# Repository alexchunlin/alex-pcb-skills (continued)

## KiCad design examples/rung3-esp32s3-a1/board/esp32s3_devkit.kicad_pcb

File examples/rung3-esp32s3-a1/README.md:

# ESP32-S3 Devkit, rev A

An open-hardware ESP32-S3 board with no module: the chip, crystal, RF match, chip antenna and power all sit on a 60 x 26 mm four-layer board. Flash it over USB-C with nothing else attached. Two 0.1 inch rows, 0.9 inch apart, fit a breadboard.

| | |
|---|---|
| Chip | ESP32-S3FH4R2, dual LX7, 2.4 GHz Wi-Fi, Bluetooth LE |
| Memory | 4 MB flash, 2 MB PSRAM, in package |
| Power | USB-C or 5 V on J2.1, 3.3 V LDO, 800 mA rated |
| Antenna | Johanson 2450AT18D0100 ceramic, on the short edge |
| I2C | Qwiic on J4, SDA GPIO17, SCL GPIO18, 10 k pull-ups, cut JP2 to remove |
| Buttons | RST, BOOT |
| LEDs | Power (red, cut JP1), user on GPIO9 (yellow) |
| Free GPIO on headers | 35, plus 3V3, 5V, EN, 2 GND |

The ESP32-S3 has no fixed I2C address. Any device you add on Qwiic sets its own.

## Pinout
Pin 1 is at the USB end. Details and strapping notes are in `PINMAP.md`.

| Pin | J1 | J2 |
|---|---|---|
| 1 | 3V3 | 5V |
| 2 | GPIO18 SCL | GND |
| 3 | GPIO17 SDA | GPIO21 |
| 4 | GPIO16 | GPIO47 |
| 5 | GPIO15 | GPIO48 |
| 6 | GPIO14 | GPIO33 |
| 7 | GPIO13 | GPIO34 |
| 8 | GPIO12 | GPIO35 |
| 9 | GPIO11 | GPIO36 |
| 10 | GPIO10 | GPIO37 |
| 11 | GPIO8 | GPIO38 |
| 12 | GPIO7 | GPIO39 |
| 13 | GPIO6 | GPIO40 |
| 14 | GPIO5 | GPIO41 |
| 15 | GPIO4 | GPIO42 |
| 16 | GPIO3 strap | GPIO43 U0TXD |
| 17 | GPIO2 | GPIO44 U0RXD |
| 18 | GPIO1 | GPIO45 strap |
| 19 | GPIO0 BOOT strap | GPIO46 strap |
| 20 | EN | GND |

## First flash
Hold BOOT, tap RST, release BOOT, then `esptool.py --chip esp32s3 write_flash ...` over USB. `BRINGUP.md` has the full sequence and the RF tuning steps. The RF match is unproven until someone tunes one on a VNA.

Keep hands and metal away from the antenna end. Do not pull GPIO45 high at reset: the flash runs at 3.3 V and needs VDD_SPI there.

## Files
`esp32s3_devkit.zen` and `blocks/` are the source. `tools/regen.sh` rebuilds the KiCad project and `fab/`. `DESIGN_LOG.md` has every calculation.

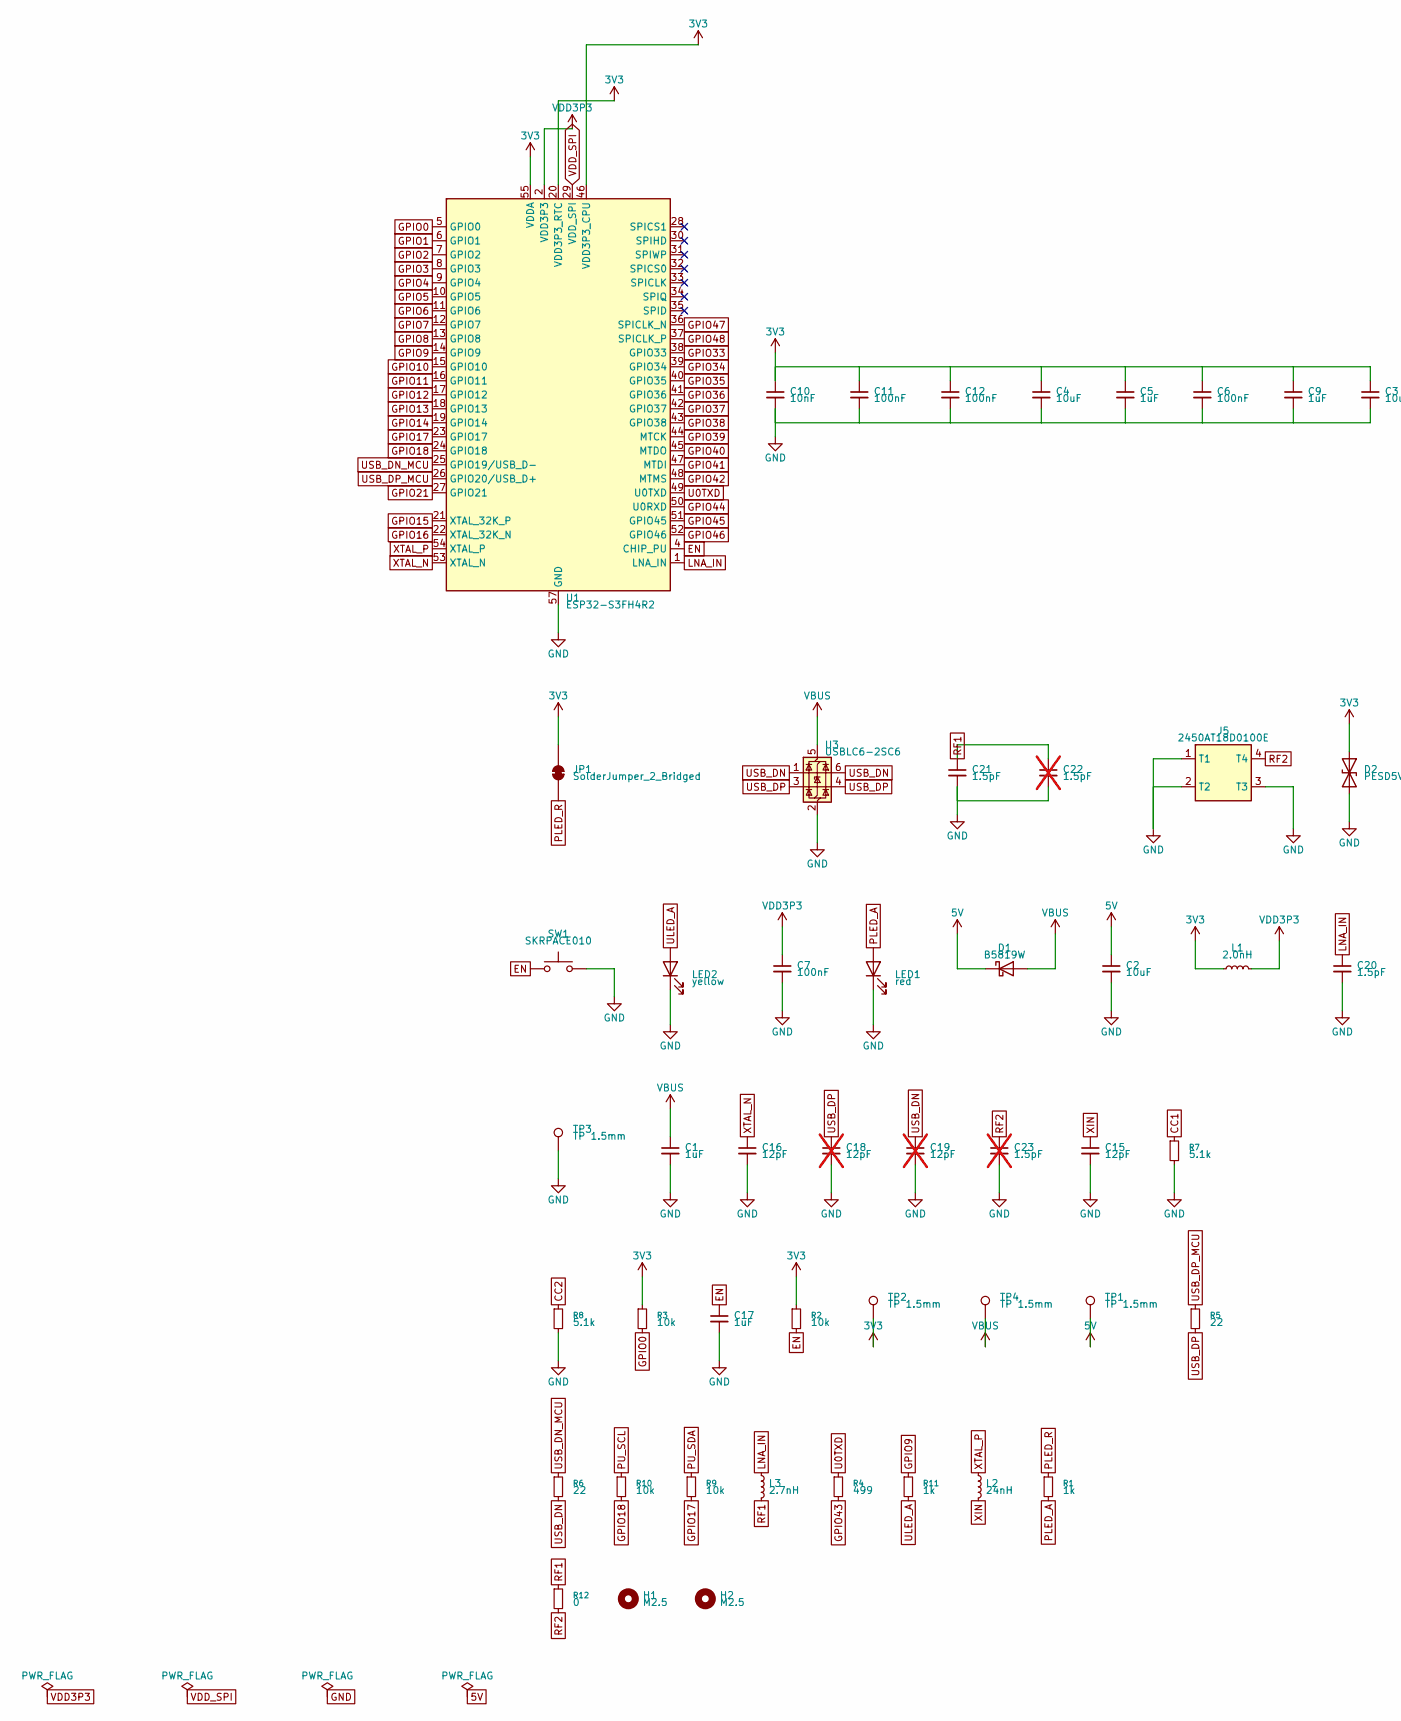
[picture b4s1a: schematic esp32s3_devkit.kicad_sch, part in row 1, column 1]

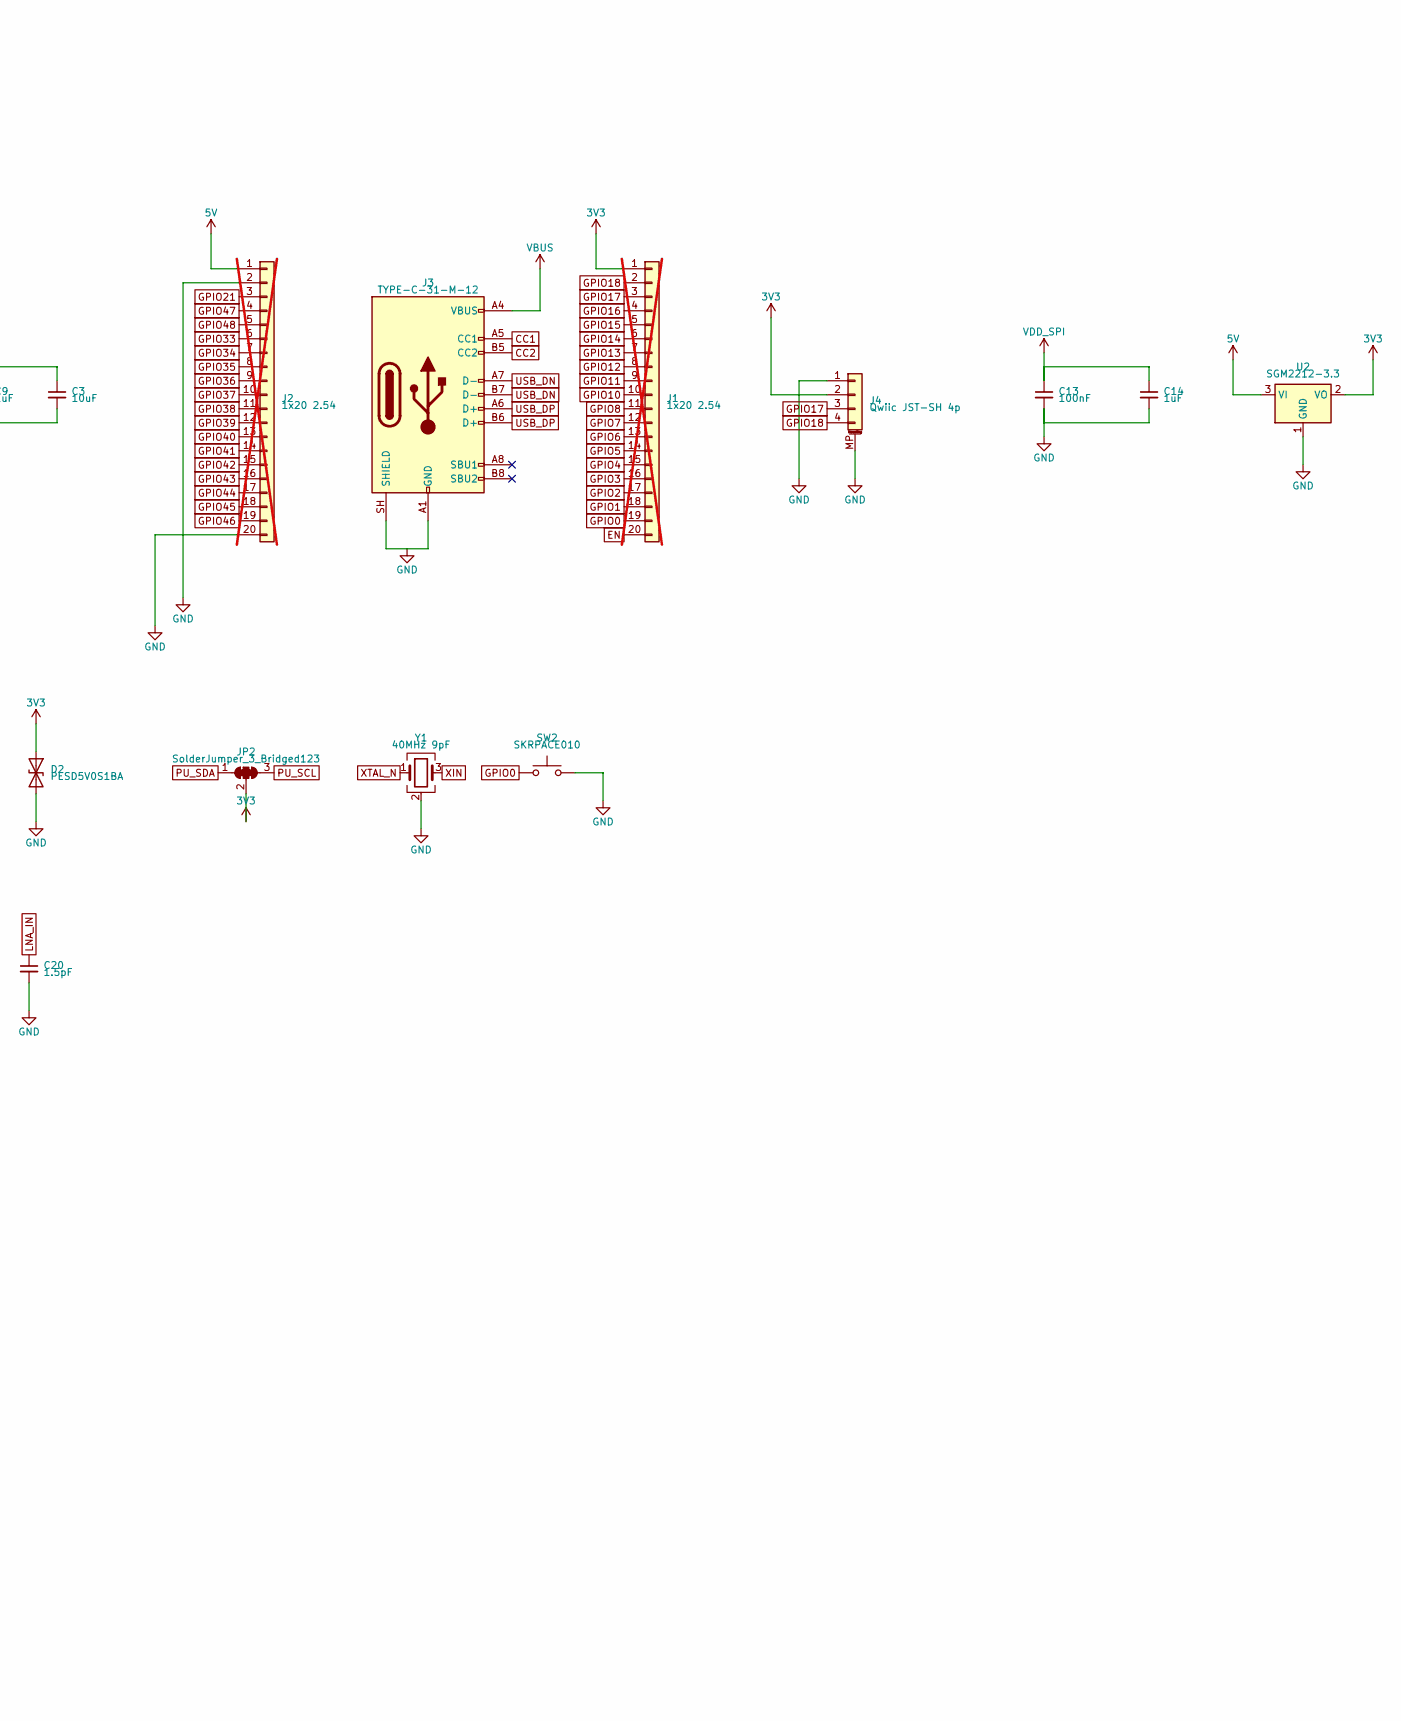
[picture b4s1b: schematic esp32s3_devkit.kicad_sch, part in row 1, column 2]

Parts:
C1, C5, C9, C14, C17: 1uF; C_0402_1005Metric; MPN CL05A105KA5NQNC; LCSC C52923
C2, C3, C4: 10uF; C_0603_1608Metric; MPN CL10A106KP8NNNC; LCSC C19702
C6, C7, C11, C12, C13: 100nF; C_0402_1005Metric; MPN CL05B104KO5NNNC; LCSC C1525
C10: 10nF; C_0402_1005Metric; MPN CL05B103KB5NNNC; LCSC C15195
C15, C16: 12pF; C_0402_1005Metric; MPN 0402CG120J500NT; LCSC C1547
C18, C19: 12pF; C_0402_1005Metric; MPN 0402CG120J500NT; LCSC C1547; not fitted
C20, C21: 1.5pF; C_0402_1005Metric; MPN GJM1555C1H1R5BB01D; LCSC C76900
C22, C23: 1.5pF; C_0402_1005Metric; MPN GJM1555C1H1R5BB01D; LCSC C76900; not fitted
D1: B5819W; D_SOD-123; MPN B5819W SL; LCSC C8598
D2: PESD5V0S1BA; D_SOD-323; MPN PESD5V0S1BA; LCSC C2827694
H1, H2: M2.5; MountingHole_2.7mm_M2.5
J1, J2: 1x20 2.54; PinHeader_1x20_P2.54mm_Vertical; MPN PZ254V-11-20P; LCSC C22465880; not fitted
J3: TYPE-C-31-M-12; USB_C_Receptacle_HRO_TYPE-C-31-M-12; MPN TYPE-C-31-M-12; LCSC C165948
J4: Qwiic JST-SH 4p; JST_SH_SM04B-SRSS-TB_1x04-1MP_P1.00mm_Horizontal; MPN SM04B-SRSS-TB(LF)(SN); LCSC C160404
J5: 2450AT18D0100E; ANT_Johanson_2450AT18D0100; MPN 2450AT18D0100E; LCSC C2917718
JP1: SolderJumper_2_Bridged; SolderJumper-2_P1.3mm_Bridged12_Pad1.0x1.5mm
JP2: SolderJumper_3_Bridged123; SolderJumper-3_P1.3mm_Bridged123_Pad1.0x1.5mm
L1: 2.0nH; L_0402_1005Metric; MPN LQG15HS2N0S02D; LCSC C18216
L2: 24nH; L_0402_1005Metric; MPN MLG1005S24NHTD25; LCSC C404641
L3: 2.7nH; L_0402_1005Metric; MPN LQG15HS2N7S02D; LCSC C77108
LED1: red; LED_0603_1608Metric; MPN KT-0603R; LCSC C2286
LED2: yellow; LED_0603_1608Metric; MPN KT-0603Y; LCSC C2287
R1, R11: 1k; R_0402_1005Metric; MPN 0402WGF1001TCE; LCSC C11702
R2, R3, R9, R10: 10k; R_0402_1005Metric; MPN RC0402FR-0710KL; LCSC C60490
R4: 499; R_0402_1005Metric; MPN 0402WGF4990TCE; LCSC C4125
R5, R6: 22; R_0402_1005Metric; MPN RC0402FR-0722RL; LCSC C114765
R7, R8: 5.1k; R_0402_1005Metric; MPN 0402WGF5101TCE; LCSC C25905
R12: 0; R_0402_1005Metric; MPN 0402WGF0000TCE; LCSC C17168
SW1, SW2: SKRPACE010; SW_Alps_SKRPACE010; MPN SKRPACE010; LCSC C139797
TP1, TP2, TP3, TP4: TP 1.5mm; TestPoint_Pad_D1.5mm_Ring1.0
U1: ESP32-S3FH4R2; QFN-56-1EP_7x7mm_P0.4mm_EP5.6x5.6mm; MPN ESP32-S3FH4R2; LCSC C3013940
U2: SGM2212-3.3; TO-252-2; MPN SGM2212-3.3XOB2G/TR; LCSC C5152863
U3: USBLC6-2SC6; SOT-23-6; MPN USBLC6-2SC6; LCSC C7519
Y1: 40MHz 9pF; Crystal_SMD_3225-4Pin_3.2x2.5mm; MPN X1E0000210177; LCSC C255943

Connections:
3V3: C3.1, C4.1, C5.1, C6.1, C9.1, C10.1, C11.1, C12.1, D2.1 (A1), J1.1, J4.2, JP1.1 (A), JP2.2 (C), L1.1, R2.1, R3.1, TP2.1, U1.20 (VDD3P3_RTC), U1.46 (VDD3P3_CPU), U1.55 (VDDA), U1.56 (VDDA), U2.2 (VO)
5V: C2.1, D1.1 (K), J2.1, TP1.1, U2.3 (VI)
CC1: J3.A5 (CC1), R7.1
CC2: J3.B5 (CC2), R8.1
EN: C17.1, J1.20, R2.2, SW1.1 (A), SW1.2 (A), U1.4 (CHIP_PU)
GND: C1.2, C2.2, C3.2, C4.2, C5.2, C6.2, C7.2, C9.2, C10.2, C11.2, C12.2, C13.2, C14.2, C15.2, C16.2, C17.2, C18.2, C19.2, C20.2, C21.2, C22.2, C23.2, D2.2 (A2), J2.2, J2.20, J3.A1 (GND), J3.A12 (GND), J3.B1 (GND), J3.B12 (GND), J3.SH (SHIELD), J4.1, J4.MP (MountPin), J5.1 (T1), J5.2 (T2), J5.3 (T3), LED1.1 (K), LED2.1 (K), R7.2, R8.2, SW1.3 (B), SW1.4 (B), SW2.3 (B), SW2.4 (B), TP3.1, U1.57 (GND), U2.1 (GND), U3.2 (GND), Y1.2 (G), Y1.4 (G)
GPIO0: J1.19, R3.2, SW2.1 (A), SW2.2 (A), U1.5 (GPIO0)
GPIO1: J1.18, U1.6 (GPIO1)
GPIO2: J1.17, U1.7 (GPIO2)
GPIO3: J1.16, U1.8 (GPIO3)
GPIO4: J1.15, U1.9 (GPIO4)
GPIO5: J1.14, U1.10 (GPIO5)
GPIO6: J1.13, U1.11 (GPIO6)
GPIO7: J1.12, U1.12 (GPIO7)
GPIO8: J1.11, U1.13 (GPIO8)
GPIO9: R11.1, U1.14 (GPIO9)
GPIO10: J1.10, U1.15 (GPIO10)
GPIO11: J1.9, U1.16 (GPIO11)
GPIO12: J1.8, U1.17 (GPIO12)
GPIO13: J1.7, U1.18 (GPIO13)
GPIO14: J1.6, U1.19 (GPIO14)
GPIO15: J1.5, U1.21 (XTAL_32K_P)
GPIO16: J1.4, U1.22 (XTAL_32K_N)
GPIO17: J1.3, J4.3, R9.2, U1.23 (GPIO17)
GPIO18: J1.2, J4.4, R10.2, U1.24 (GPIO18)
GPIO21: J2.3, U1.27 (GPIO21)
GPIO33: J2.6, U1.38 (GPIO33)
GPIO34: J2.7, U1.39 (GPIO34)
GPIO35: J2.8, U1.40 (GPIO35)
GPIO36: J2.9, U1.41 (GPIO36)
GPIO37: J2.10, U1.42 (GPIO37)
GPIO38: J2.11, U1.43 (GPIO38)
GPIO39: J2.12, U1.44 (MTCK)
GPIO40: J2.13, U1.45 (MTDO)
GPIO41: J2.14, U1.47 (MTDI)
GPIO42: J2.15, U1.48 (MTMS)
GPIO43: J2.16, R4.2
GPIO44: J2.17, U1.50 (U0RXD)
GPIO45: J2.18, U1.51 (GPIO45)
GPIO46: J2.19, U1.52 (GPIO46)
GPIO47: J2.4, U1.36 (SPICLK_N)
GPIO48: J2.5, U1.37 (SPICLK_P)
LNA_IN: C20.1, L3.1, U1.1 (LNA_IN)
MCU.U1.NC_U_SPICLK: U1.33 (SPICLK)
MCU.U1.NC_U_SPICS0: U1.32 (SPICS0)
MCU.U1.NC_U_SPICS1: U1.28 (SPICS1)
MCU.U1.NC_U_SPID: U1.35 (SPID)
MCU.U1.NC_U_SPIHD: U1.30 (SPIHD)
MCU.U1.NC_U_SPIQ: U1.34 (SPIQ)
MCU.U1.NC_U_SPIWP: U1.31 (SPIWP)
PLED_A: LED1.2 (A), R1.2
PLED_R: JP1.2 (B), R1.1
PU_SCL: JP2.3 (B), R10.1
PU_SDA: JP2.1 (A), R9.1
RF1: C21.1, C22.1, L3.2, R12.1
RF2: C23.1, J5.4 (T4), R12.2
U0TXD: R4.1, U1.49 (U0TXD)
ULED_A: LED2.2 (A), R11.2
USB.J3.NC_J_SBU1: J3.A8 (SBU1)
USB.J3.NC_J_SBU2: J3.B8 (SBU2)
USB_DN: C19.1, J3.A7 (D-), J3.B7 (D-), R6.2, U3.1 (I/O1), U3.6 (I/O1)
USB_DN_MCU: R6.1, U1.25 (GPIO19/USB_D-)
USB_DP: C18.1, J3.A6 (D+), J3.B6 (D+), R5.2, U3.3 (I/O2), U3.4 (I/O2)
USB_DP_MCU: R5.1, U1.26 (GPIO20/USB_D+)
VBUS: C1.1, D1.2 (A), J3.A4 (VBUS), J3.A9 (VBUS), J3.B4 (VBUS), J3.B9 (VBUS), TP4.1, U3.5 (VBUS)
VDD3P3: C7.1, L1.2, U1.2 (VDD3P3), U1.3 (VDD3P3)
VDD_SPI: C13.1, C14.1, U1.29 (VDD_SPI)
XIN: C15.1, L2.2, Y1.3
XTAL_N: C16.1, U1.53 (XTAL_N), Y1.1
XTAL_P: L2.1, U1.54 (XTAL_P)

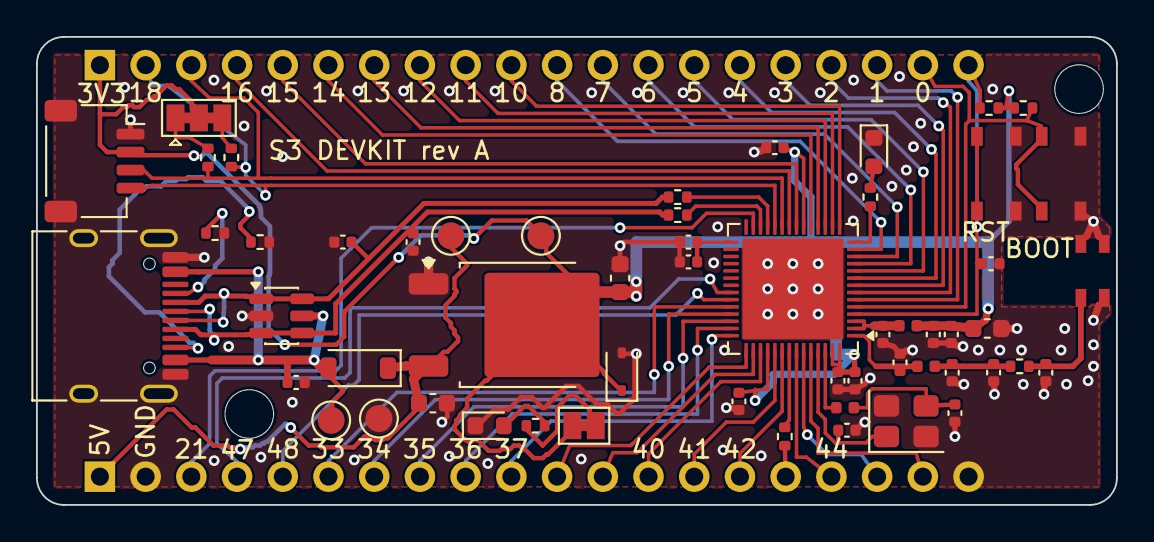
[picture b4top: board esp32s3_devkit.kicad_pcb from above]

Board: 4 copper layers, 60.0 x 26.0 mm, 60 parts (0 on the bottom side), 61 nets.

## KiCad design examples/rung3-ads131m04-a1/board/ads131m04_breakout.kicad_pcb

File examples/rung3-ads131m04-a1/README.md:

# ADS131M04 four-channel simultaneous 24-bit ADC breakout

TI ADS131M04 on a 40 x 25.4 mm board: four differential channels sampled at the same instant, 24 bits, up to 64 kSPS, over SPI. For vibration, power and sensor logging. 8.192 MHz oscillator on board. Two 0.1 inch headers 0.9 inch apart straddle a breadboard.

| What | Value |
|---|---|
| Input | +/-1.2 V differential at gain 1, to +/-9.375 mV at gain 128. Absolute limits AGND - 1.3 V to AVDD at gain 1 to 4 |
| Filter | 1 k + 1 k + 10 nF C0G per channel, corner 7.96 kHz. Change the cap to 2.2 nF C0G (LCSC C33353) for 36 kHz |
| Noise | 10.68 uVrms at 16 kSPS, gain 1; 0.42 uVrms at 250 SPS, gain 32 to 128 (Table 7-1) |
| Power | VIN 3.3 to 5 V, about 11 mA. 3V3 pin is an output, 100 mA for your circuit |
| Logic | 3.3 V only, not 5 V tolerant |
| SPI | Mode 1, to 25 MHz SCLK. At 64 kSPS with 24-bit words, 9.2 MHz minimum |

| J2 pin | Name | Function | | J1 pin | Name | Function |
|---|---|---|---|---|---|---|
| 1 | VIN | 3.3 to 5 V in | | 1 | AIN0P | Channel 0 + |
| 2 | 3V3 | 3.3 V out | | 2 | AIN0N | Channel 0 - |
| 3 | GND | Ground | | 3 | GND | Ground |
| 4 | DIN | SPI data in | | 4 | AIN1N | Channel 1 - |
| 5 | DOUT | SPI data out | | 5 | AIN1P | Channel 1 + |
| 6 | SCLK | SPI clock | | 6 | GND | Ground |
| 7 | DRDY | Data ready, active low | | 7 | AIN2P | Channel 2 + |
| 8 | CS | Chip select, active low, 10 k pull-up | | 8 | AIN2N | Channel 2 - |
| 9 | SYNC | SYNC/RESET, active low, 10 k pull-up | | 9 | GND | Ground |
| 10 | GND | Ground | | 10 | AIN3N | Channel 3 - |
| | | | | 11 | AIN3P | Channel 3 + |

J1 follows the ADC's pin order, so channels 1 and 3 read N then P. Check the silk on the back.

SPI, so no I2C address and no Qwiic. Cut JP1 to turn the power LED off. For two boards to sample together, tie SYNC together and pulse it; each board has its own oscillator, so they drift apart by up to 40 ppm between pulses.

Hardware files: `layout/ads131m04_breakout/`, fabrication package in `fab/`. Source is `ads131m04_breakout.zen` and `blocks/`; `tools/regen.sh` rebuilds everything. Bring-up steps are in `BRINGUP.md`.

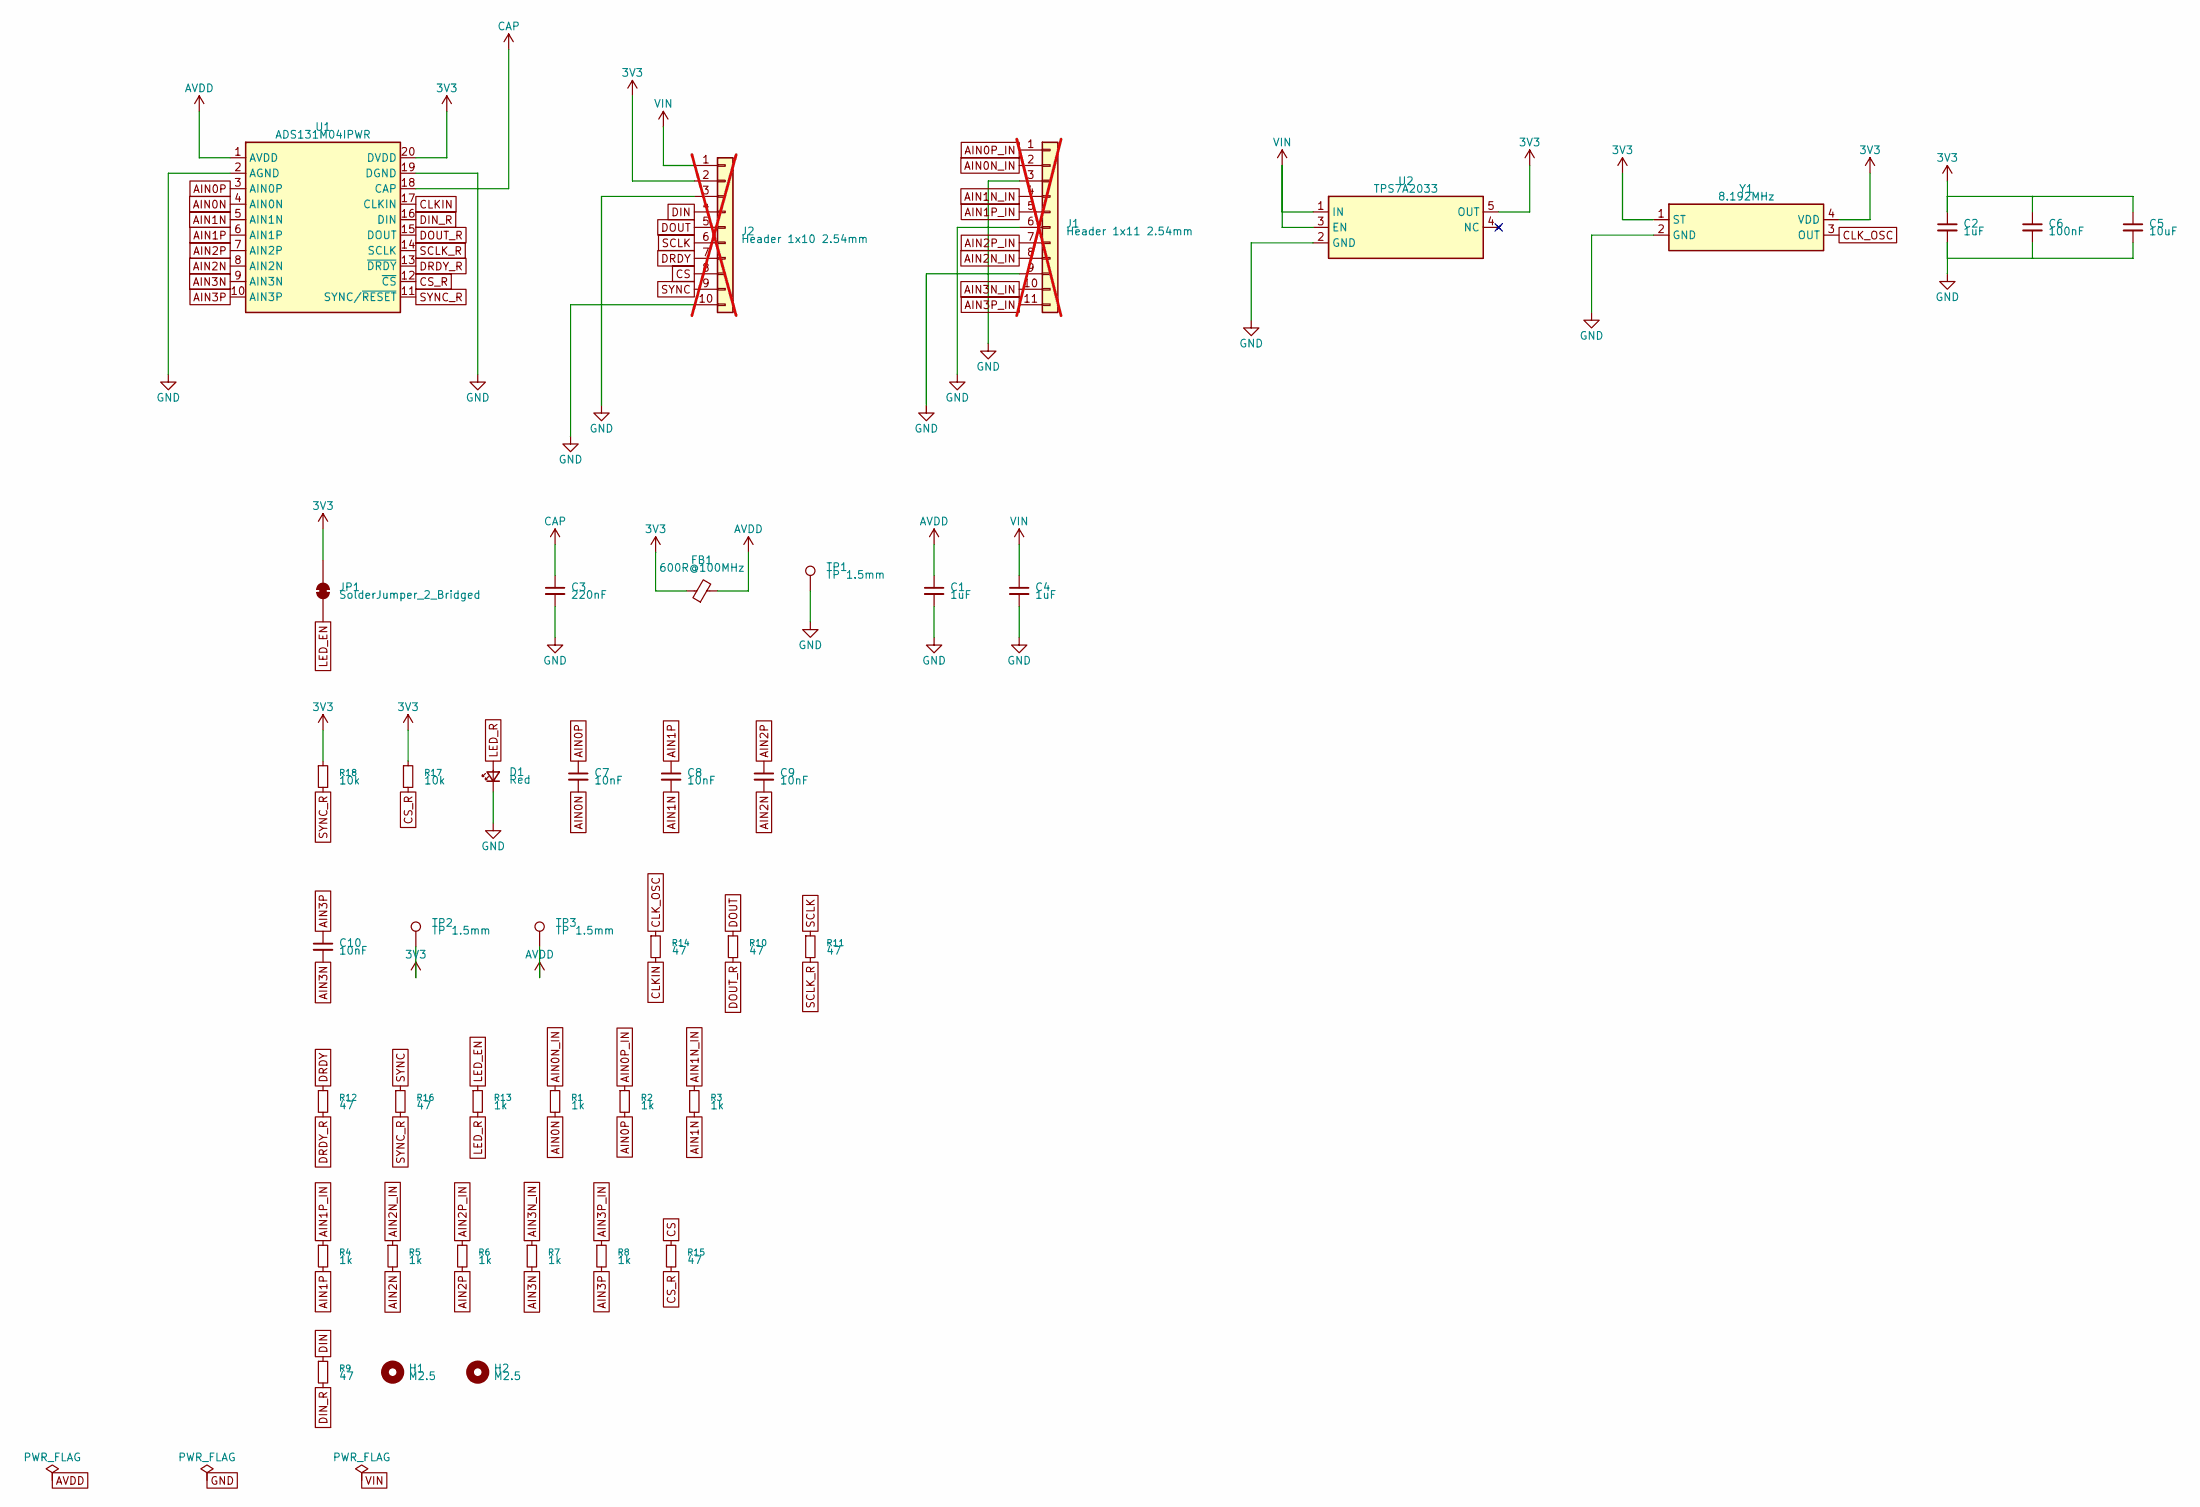
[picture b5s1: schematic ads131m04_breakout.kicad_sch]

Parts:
C1, C2, C4: 1uF; C_0603_1608Metric; MPN CL10A105KB8NNNC; LCSC C15849
C3: 220nF; C_0603_1608Metric; MPN CL10B224KA8NNNC; LCSC C21120
C5: 10uF; C_0603_1608Metric; MPN CL10A106KP8NNNC; LCSC C19702
C6: 100nF; C_0603_1608Metric; MPN CC0603KRX7R9BB104; LCSC C14663
C7, C8, C9, C10: 10nF; C_0603_1608Metric; MPN GRM1885C1H103JA01D; LCSC C85973
D1: Red; LED_0603_1608Metric; MPN KT-0603R; LCSC C2286
FB1: 600R@100MHz; L_0603_1608Metric; MPN GZ1608D601TF; LCSC C1002
H1, H2: M2.5; MountingHole_2.7mm_M2.5
J1: Header 1x11 2.54mm; PinHeader_1x11_P2.54mm_Vertical; MPN PZ254V-11-11P; LCSC C2840011; not fitted
J2: Header 1x10 2.54mm; PinHeader_1x10_P2.54mm_Vertical; MPN PZ254V-11-10P; LCSC C492409; not fitted
JP1: SolderJumper_2_Bridged; SolderJumper-2_P1.3mm_Bridged12_Pad1.0x1.5mm
R1, R2, R3, R4, R5, R6, R7, R8, R13: 1k; R_0603_1608Metric; MPN 0603WAF1001T5E; LCSC C21190
R9, R10, R11, R12, R14, R15, R16: 47; R_0603_1608Metric; MPN 0603WAF470JT5E; LCSC C23182
R17, R18: 10k; R_0603_1608Metric; MPN 0603WAF1002T5E; LCSC C25804
TP1, TP2, TP3: TP 1.5mm; TestPoint_Pad_D1.5mm_Ring1.0
U1: ADS131M04IPWR; Texas_PW0020A_TSSOP-20_4.4x6.5mm_P0.65mm; MPN ADS131M04IPWR; LCSC C2862562
U2: TPS7A2033; SOT-23-5; MPN TPS7A2033PDBVR; LCSC C2862740
Y1: 8.192MHz; Oscillator_YXC_YSO110TR_3225; MPN OT2JI-111-8.192M; LCSC C7425393

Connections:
3V3: C2.1, C5.1, C6.1, FB1.1, J2.2, JP1.1 (A), R17.1, R18.1, TP2.1, U1.20 (DVDD), U2.5 (OUT), Y1.1 (ST), Y1.4 (VDD)
AIN0N: C7.2, R1.2, U1.4 (AIN0N)
AIN0N_IN: J1.2, R1.1
AIN0P: C7.1, R2.2, U1.3 (AIN0P)
AIN0P_IN: J1.1, R2.1
AIN1N: C8.2, R3.2, U1.5 (AIN1N)
AIN1N_IN: J1.4, R3.1
AIN1P: C8.1, R4.2, U1.6 (AIN1P)
AIN1P_IN: J1.5, R4.1
AIN2N: C9.2, R5.2, U1.8 (AIN2N)
AIN2N_IN: J1.8, R5.1
AIN2P: C9.1, R6.2, U1.7 (AIN2P)
AIN2P_IN: J1.7, R6.1
AIN3N: C10.2, R7.2, U1.9 (AIN3N)
AIN3N_IN: J1.10, R7.1
AIN3P: C10.1, R8.2, U1.10 (AIN3P)
AIN3P_IN: J1.11, R8.1
AVDD: C1.1, FB1.2, TP3.1, U1.1 (AVDD)
CAP: C3.1, U1.18 (CAP)
CLKIN: R14.2, U1.17 (CLKIN)
CLK_OSC: R14.1, Y1.3 (OUT)
CS: J2.8, R15.1
CS_R: R15.2, R17.2, U1.12 (~CS)
DIN: J2.4, R9.1
DIN_R: R9.2, U1.16 (DIN)
DOUT: J2.5, R10.1
DOUT_R: R10.2, U1.15 (DOUT)
DRDY: J2.7, R12.1
DRDY_R: R12.2, U1.13 (~DRDY)
GND: C1.2, C2.2, C3.2, C4.2, C5.2, C6.2, D1.1 (K), J1.3, J1.6, J1.9, J2.3, J2.10, TP1.1, U1.2 (AGND), U1.19 (DGND), U2.2 (GND), Y1.2 (GND)
LED_EN: JP1.2 (B), R13.1
LED_R: D1.2 (A), R13.2
POWER.U2.NC_U_NC: U2.4 (NC)
SCLK: J2.6, R11.1
SCLK_R: R11.2, U1.14 (SCLK)
SYNC: J2.9, R16.1
SYNC_R: R16.2, R18.2, U1.11 (SYNC/~RESET)
VIN: C4.1, J2.1, U2.1 (IN), U2.3 (EN)

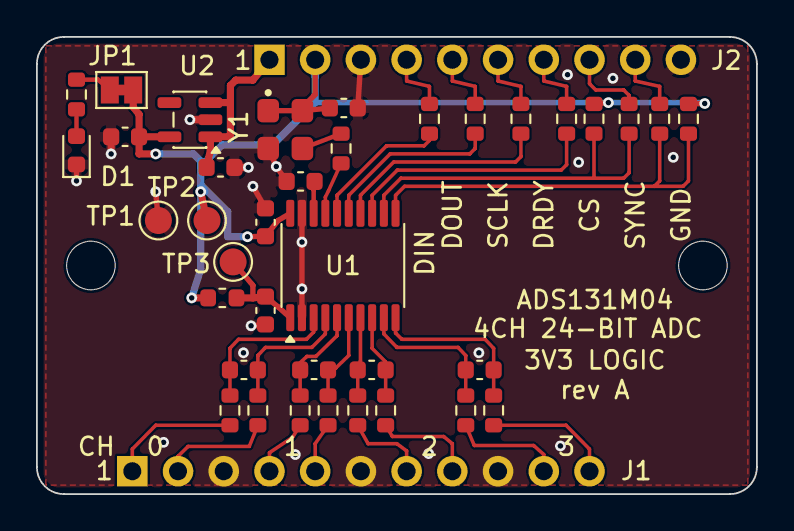
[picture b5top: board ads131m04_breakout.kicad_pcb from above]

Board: 4 copper layers, 40.0 x 25.4 mm, 41 parts (0 on the bottom side), 37 nets.

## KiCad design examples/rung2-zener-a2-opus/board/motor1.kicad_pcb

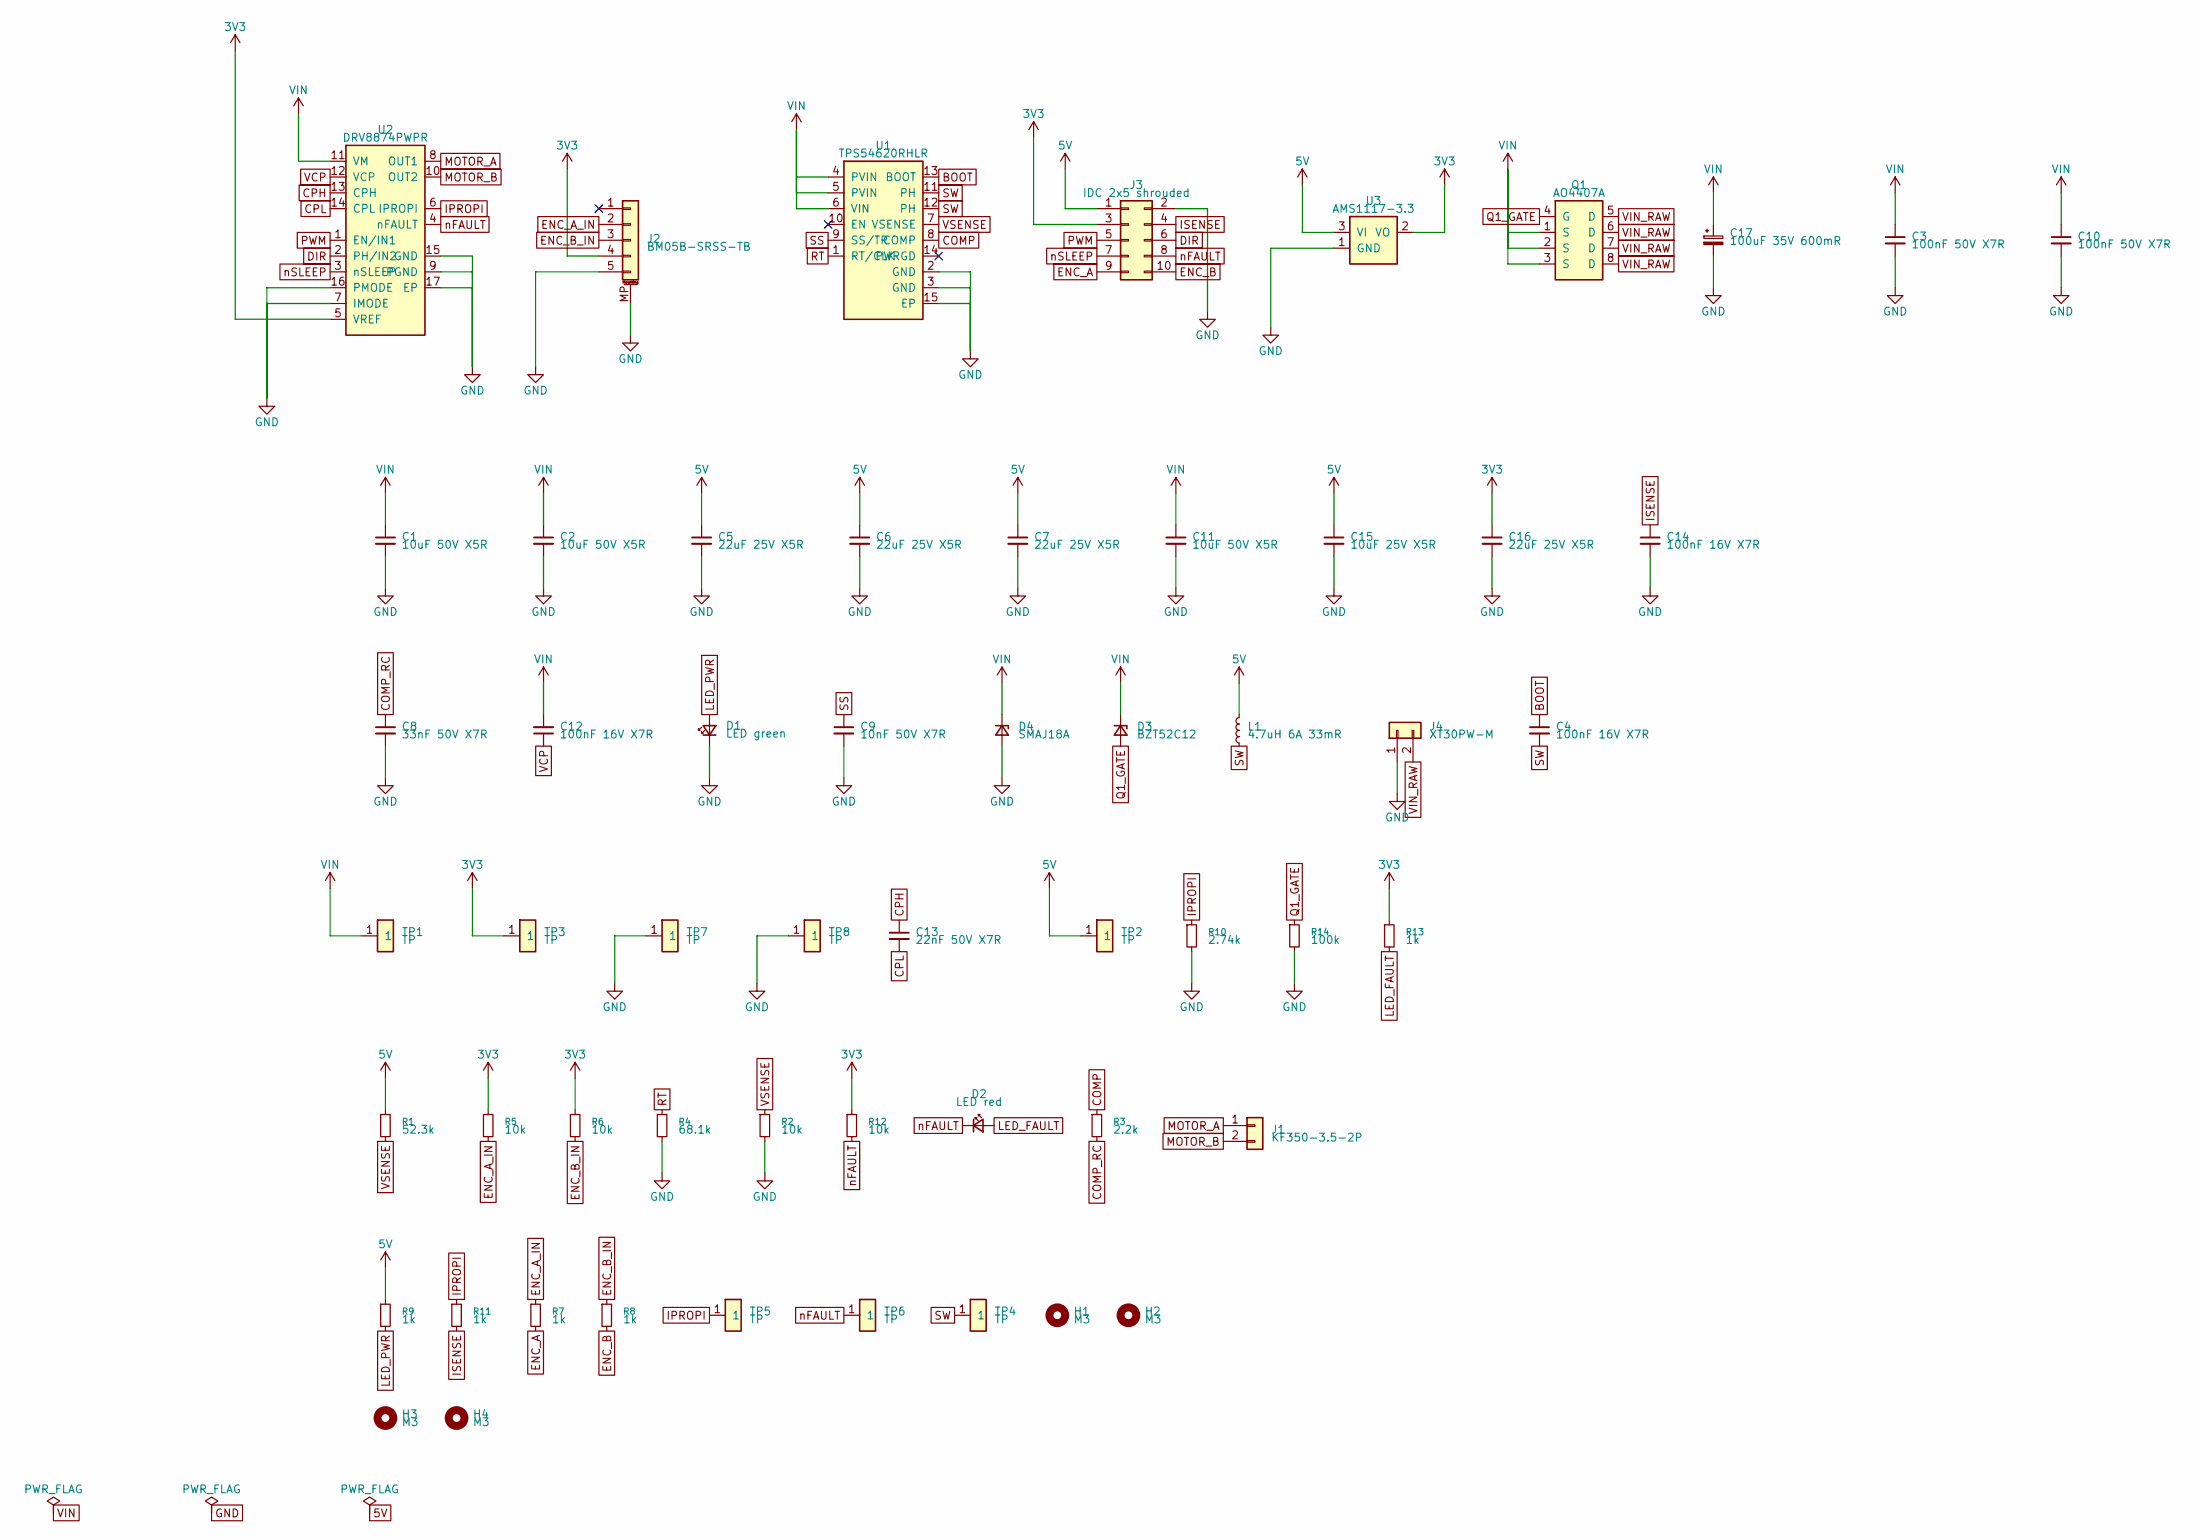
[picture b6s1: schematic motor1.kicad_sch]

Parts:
C1, C2, C11: 10uF 50V X5R; C_1206_3216Metric; MPN CL31A106KBHNNNE; LCSC C13585
C3, C10: 100nF 50V X7R; C_0603_1608Metric; MPN CC0603KRX7R9BB104; LCSC C14663
C4, C12, C14: 100nF 16V X7R; C_0402_1005Metric; MPN CL05B104KO5NNNC; LCSC C1525
C5, C6, C7, C16: 22uF 25V X5R; C_0805_2012Metric; MPN CL21A226MAQNNNE; LCSC C45783
C8: 33nF 50V X7R; C_0402_1005Metric; MPN FCC0402B333K500AT; LCSC C7419416
C9: 10nF 50V X7R; C_0402_1005Metric; MPN CL05B103KB5NNNC; LCSC C15195
C13: 22nF 50V X7R; C_0402_1005Metric; MPN CL05B223KB5NNNC; LCSC C337699
C15: 10uF 25V X5R; C_0805_2012Metric; MPN CL21A106KAYNNNE; LCSC C15850
C17: 100uF 35V 600mR; CP_Elec_6.3x7.7; MPN RVE100UF35V67RV0072; LCSC C2836437
D1: LED green; LED_0603_1608Metric; MPN KT-0603G; LCSC C12624
D2: LED red; LED_0603_1608Metric; MPN KT-0603R; LCSC C2286
D3: BZT52C12; D_SOD-123; MPN BZT52C12; LCSC C173429
D4: SMAJ18A; D_SMA; MPN SMAJ18A; LCSC C148219
H1, H2, H3, H4: M3; MountingHole_3.2mm_M3
J1: KF350-3.5-2P; TerminalBlock_Phoenix_PT-1,5-2-3.5-H_1x02_P3.50mm_Horizontal; MPN KF350-3.5-2P; LCSC C474892
J2: BM05B-SRSS-TB; JST_SH_BM05B-SRSS-TB_1x05-1MP_P1.00mm_Vertical; MPN BM05B-SRSS-TB(LF)(SN); LCSC C265092
J3: IDC 2x5 shrouded; IDC-Header_2x05_P2.54mm_Vertical; MPN XDFH-0254-2*5P; LCSC C19193807
J4: XT30PW-M; AMASS_XT30PW-M_1x02_P2.50mm_Horizontal; MPN XT30PW-M30.G.Y; LCSC C431092
L1: 4.7uH 6A 33mR; L_Changjiang_FXL0630; MPN FXL0630-4R7-M; LCSC C167220
Q1: AO4407A; SOIC-8_3.9x4.9mm_P1.27mm; MPN AO4407A; LCSC C16072
R1: 52.3k; R_0402_1005Metric; MPN 0402WGF5232TCE; LCSC C26982
R2, R5, R6, R12: 10k; R_0402_1005Metric; MPN 0402WGF1002TCE; LCSC C25744
R3: 2.2k; R_0402_1005Metric; MPN 0402WGF2201TCE; LCSC C25879
R4: 68.1k; R_0402_1005Metric; MPN 0402WGF6812TCE; LCSC C11537
R7, R8, R9, R11, R13: 1k; R_0402_1005Metric; MPN 0402WGF1001TCE; LCSC C11702
R10: 2.74k; R_0402_1005Metric; MPN 0402WGF2741TCE; LCSC C33360
R14: 100k; R_0402_1005Metric; MPN 0402WGF1003TCE; LCSC C25741
TP1, TP2, TP3, TP4, TP5, TP6, TP7, TP8: TP; TestPoint_Pad_D1.5mm
U1: TPS54620RHLR; TPS54620RHL_VQFN-14_3.5x3.5; MPN TPS54620RHLR; LCSC C263274
U2: DRV8874PWPR; HTSSOP-16-1EP_4.4x5mm_P0.65mm_EP3.4x5mm_Mask2.46x2.31mm; MPN DRV8874PWPR; LCSC C1855818
U3: AMS1117-3.3; SOT-223-3_TabPin2; MPN AMS1117-3.3; LCSC C6186

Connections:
3V3: C16.1, J2.4, J3.3, R5.1, R6.1, R12.1, R13.1, TP3.1, U2.5 (VREF), U3.2 (VO)
5V: C5.1, C6.1, C7.1, C15.1, J3.1, L1.2, R1.1, R9.1, TP2.1, U3.3 (VI)
BOOT: C4.1, U1.13 (BOOT)
BUCK.NC_U1_EN: U1.10 (EN)
BUCK.NC_U1_PWRGD: U1.14 (PWRGD)
COMP: R3.1, U1.8 (COMP)
COMP_RC: C8.1, R3.2
CONN.NC_J2_Pin_1: J2.1
CPH: C13.1, U2.13 (CPH)
CPL: C13.2, U2.14 (CPL)
DIR: J3.6, U2.2 (PH/IN2)
ENC_A: J3.9, R7.2
ENC_A_IN: J2.2, R5.2, R7.1
ENC_B: J3.10, R8.2
ENC_B_IN: J2.3, R6.2, R8.1
GND: C1.2, C2.2, C3.2, C5.2, C6.2, C7.2, C8.2, C9.2, C10.2, C11.2, C14.2, C15.2, C16.2, C17.2, D1.1 (K), D4.2 (A), J2.5, J2.MP (MountPin), J3.2, J4.1, R2.2, R4.2, R10.2, R14.2, TP7.1, TP8.1, U1.2 (GND), U1.3 (GND), U1.15 (EP), U2.7 (IMODE), U2.9 (PGND), U2.15 (GND), U2.16 (PMODE), U2.17 (EP), U3.1 (GND)
IPROPI: R10.1, R11.1, TP5.1, U2.6 (IPROPI)
ISENSE: C14.1, J3.4, R11.2
LED_FAULT: D2.2 (A), R13.2
LED_PWR: D1.2 (A), R9.2
MOTOR_A: J1.1, U2.8 (OUT1)
MOTOR_B: J1.2, U2.10 (OUT2)
PWM: J3.5, U2.1 (EN/IN1)
Q1_GATE: D3.2 (A), Q1.4 (G), R14.1
RT: R4.1, U1.1 (RT/CLK)
SS: C9.1, U1.9 (SS/TR)
SW: C4.2, L1.1, TP4.1, U1.11 (PH), U1.12 (PH)
VCP: C12.1, U2.12 (VCP)
VIN: C1.1, C2.1, C3.1, C10.1, C11.1, C12.2, C17.1, D3.1 (K), D4.1 (K), Q1.1 (S), Q1.2 (S), Q1.3 (S), TP1.1, U1.4 (PVIN), U1.5 (PVIN), U1.6 (VIN), U2.11 (VM)
VIN_RAW: J4.2, Q1.5 (D), Q1.6 (D), Q1.7 (D), Q1.8 (D)
VSENSE: R1.2, R2.1, U1.7 (VSENSE)
nFAULT: D2.1 (K), J3.8, R12.2, TP6.1, U2.4 (nFAULT)
nSLEEP: J3.7, U2.3 (nSLEEP)

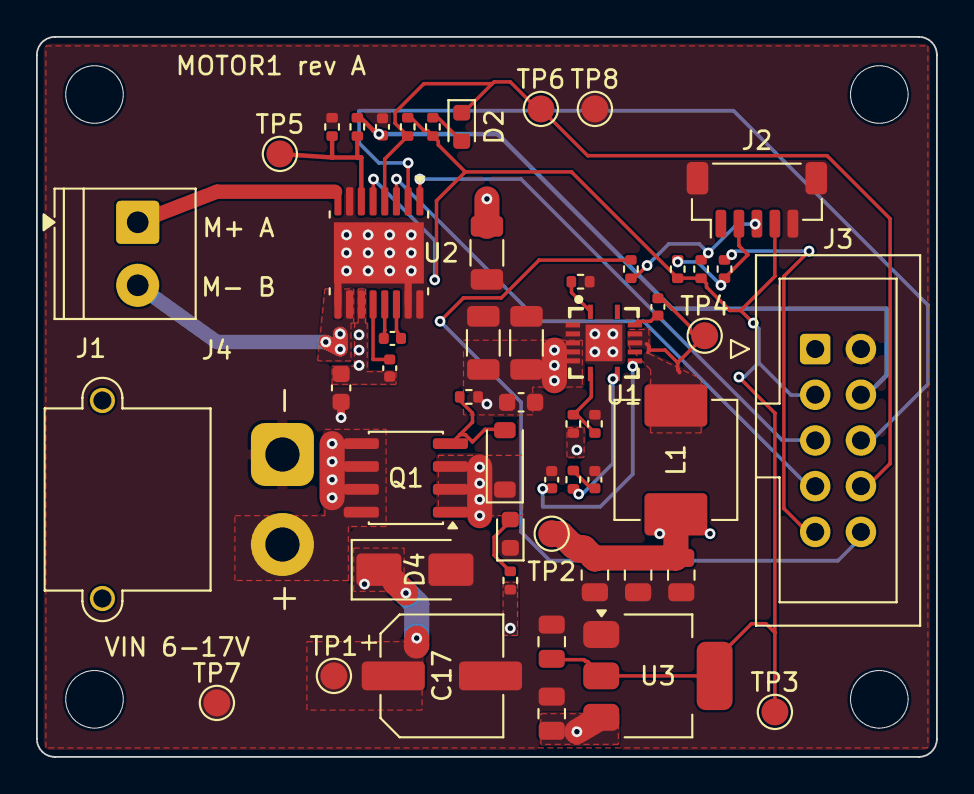
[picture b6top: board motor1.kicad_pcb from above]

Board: 4 copper layers, 50.0 x 40.0 mm, 56 parts (0 on the bottom side), 30 nets.
